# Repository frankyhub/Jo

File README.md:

<div align="center">

|[:skull:ISSUE](https://github.com/frankyhub/Jo/issues?q=is%3Aissue)|[:speech_balloon: Forum /Discussion](https://github.com/frankyhub/Jo/discussions)|[:grey_question:WiKi](https://github.com/frankyhub/Jo/wiki)||
|--|--|--|--|
| | | | |
<a href="https://github.com/frankyhub/Jo/issues">|<a href="https://github.com/frankyhub/Jo/discussions">|<a href="https://github.com/frankyhub/Jo/6eleases">||
|| <a href="https://github.com/frankyhub/Jo/pulse" alt="Activity">| <a href="https://github.com/frankyhub/Jo/graphs/traffic">  |<a href="https://github.com/frankyhub?tab=stars"> ||

<br> <br>

</div>

## Story
Diese Bauanleitung beschreibt einen tanzenden Bot. Jedes Bein hat zwei Gelenke die von Servo-Motoren bewegt werden. Als Steuerung dient ein Arduino NANO, gespeist von einer 9V-Batterie. Das Programm kann um eine Hindernis-Erkennung erweitert werden, da beim Bot auch ein Ultraschall-Sensor verbaut ist.
Die Bot-Elemente werden aus einer 2mm ABS-Platte und einer 2mm Sperrholzplatte (Füße) gelasert. Die Montage erfordert etwas Geschick.

### Bauanleitung

### Hardware

| Anzahl | Bezeichnung | 
| -------- | -------- | 
| 1  | ABS Platte DINA4 2mm   |
| 4  |  Platinenhalter (3D-Druck)  |
| 4  | Abstandshalter M3*25 Kunststoff   |
|  1 | Ardunio NANO   |
|  4 | SG90 Servo   |
|  1 |  HCSR04 Ultraschallsensor  |
|  1 | LM 2596S Spannungsregler 5V   |
|  1 |  9V Batterie mit Gehäuse  |
| ---  | ---   |

#### Schrauben

| Anzahl | Bezeichnung | 
| -------- | -------- | 
| 10  | M1.5x5 |
| 6  |  M1.4x8  |
| 12   | M2x8   |
| 12  |  M2x8  |
| 18  |  M3x5  |
| 8  |  M3x8 Senkkopf  |
| ---  | ---   |

#### Muttern

| Anzahl | Bezeichnung | 
| -------- | -------- | 
| 6  | M1.4  |
| 12  |  M2  |
| 8  |  M3 selbstsichernd  |
|  --- |  ---  |

### Schritt 1: 

- Die ABS-Platten lasern, Verwende die lbrn Vorlagen

<br> <br>

### Schritt 2: 

- Die Schenkel der Fersen und der Füße biegen und auf angegebenen Durchmesser aufbohren.

- Füße: Beide Schenkel gleich lang, Innenmaß 37 mm

<br> <br>

- Bohrungen:

<br> <br>

- Ferse biegen, beide Schenkel gleich lang:

<br> <br>

- Bohrungen: Für die 1,5mm Bohrungen des Servos, den Servo als Bohrschablone verwenden.

<br> <br>

### Schritt 3: Die Platinenhalter drucken

### Schritt 4: Die Schrittmotoren auf die Grundplatte und an die Fersen montieren und verschrauben (alternativ kleben). 
Ferse und Schenkel verschrauben. Die Teile müssen beweglich bleiben, so dass der Schrittmotor den Schenkel bewegen kann.

<br> <br>

<br> <br>

### Schritt 5: Den Ultraschallsensor an die Deckplatte montieren (alternativ kleben).

### Schritt 6: Den Arduino NANO auf die Deckplatte montieren.

<br> <br>

### Schritt 7: Den Batteriehalter an die Grundplatte montieren (alternativ kleben).

<br> <br>

### Schritt 8: Die Schrittmotoren, den Ultraschallsensor und den Batteriehalter nach Schaltplan verdrahten.

<br> <br>

### Schritt 9: Das Programm in den Arduino NANO laden

### Schritt 10: Funktionstest

---

<div style="position:absolute; left:2cm; ">   
<ol class="breadcrumb" style="border-top: 2px solid black;border-bottom:2px solid black; height: 45px; width: 900px;"> <p align="center"><a href="#oben">nach oben</a></p></ol>
</div>  

---

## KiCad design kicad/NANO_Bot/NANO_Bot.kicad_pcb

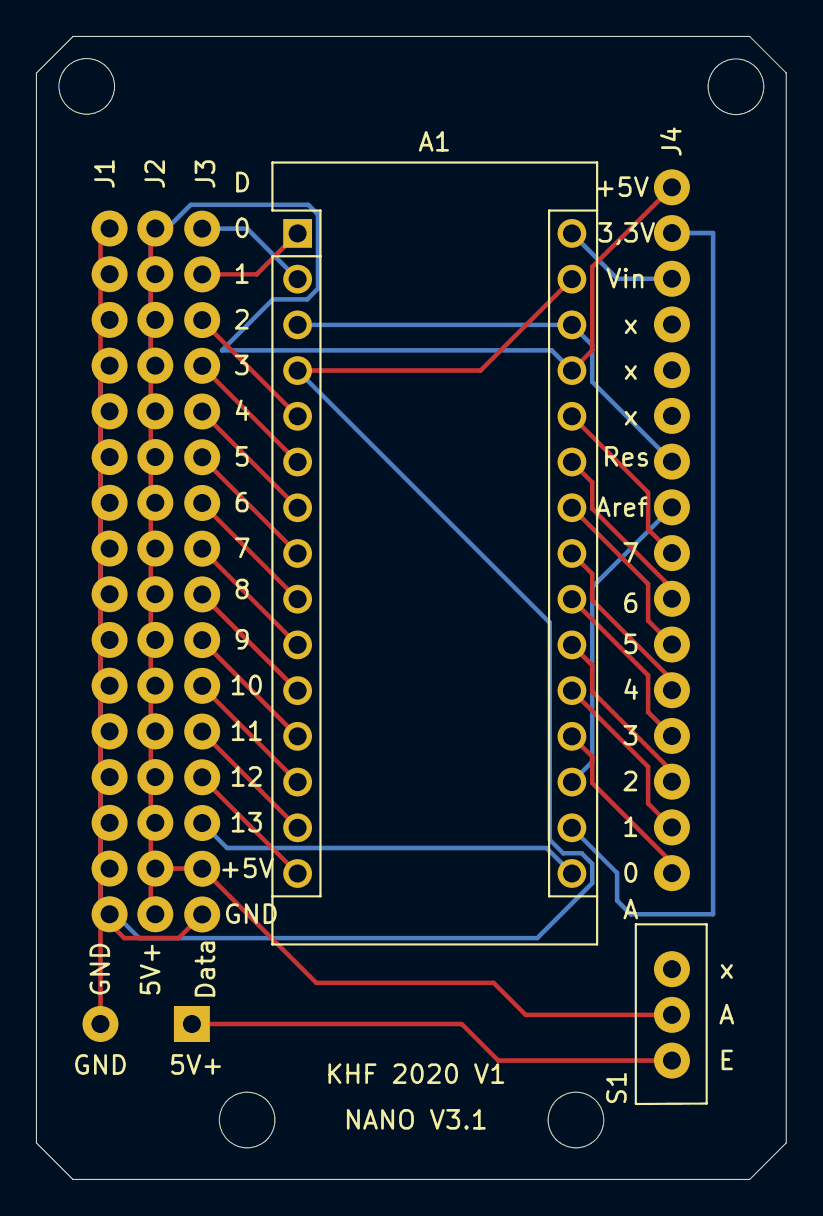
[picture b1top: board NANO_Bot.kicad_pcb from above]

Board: 2 copper layers, 41.7 x 63.5 mm, 7 parts (0 on the bottom side), 29 nets.

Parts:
A1: Arduino_Nano_v3.x; Arduino_Nano
GND: 9VBat; 9VBAT_khf
J1, J2, J3, J4: NANO16PINStiftleiste; NANO_Stift_16PIN
S1: Micro_Schalter; Micro_SchalterKHF

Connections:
unnamed: A1.1, J3.2
unnamed: A1.2, J3.1
unnamed: A1.5, J3.3
unnamed: A1.6, J3.4
unnamed: A1.7, J3.5
unnamed: A1.8, J3.6
unnamed: A1.9, J3.7
unnamed: A1.10, J3.8
unnamed: A1.11, J3.9
unnamed: A1.12, J3.10
unnamed: A1.13, J3.11
unnamed: A1.14, J3.12
unnamed: A1.15, J3.13
unnamed: A1.16, J3.14
unnamed: A1.17, J4.15
unnamed: A1.18, J4.9
unnamed: A1.19, J4.1
unnamed: A1.20, J4.2
unnamed: A1.21, J4.3
unnamed: A1.22, J4.4
unnamed: A1.23, J4.5
unnamed: A1.24, J4.6
unnamed: A1.25, J4.7
unnamed: A1.26, J4.8
unnamed: A1.27, J2.1, J2.2, J2.3, J2.4, J2.5, J2.6, J2.7, J2.8, J2.9, J2.10, J2.11, J2.12, J2.13, J2.14, J2.15, J2.16, J3.15, J4.16, S1.2
unnamed: A1.3, A1.28, J4.10
unnamed: A1.4, A1.29, GND.1, J1.1, J1.2, J1.3, J1.4, J1.5, J1.6, J1.7, J1.8, J1.9, J1.10, J1.11, J1.12, J1.13, J1.14, J1.15, J1.16, J3.16
unnamed: A1.30, J4.14
unnamed: GND.2, S1.1

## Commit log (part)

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2024-06-10 V 10.06.2024
2024-10-12 V12102024
